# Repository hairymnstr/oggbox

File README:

OggBox
======

Author: nathan@nathandumont.com
License: C code GPL V3, schematics CC-BY-SA 3.0

The OggBox is an open hardware music player.  It supports OggVorbis and WAV files
using a dedicated codec chip from VLSI.  The source code for the main processor
(an ARM Cortex) is written in C and can be found under src/firmware.  You can
compile it with a toolchain built with
https://github.com/esden/summon-arm-toolchain and can be flashed to an STM32 with
the http://code.google.com/p/stm32flash/ executable.  You may need to adjust the
Makefile as the install target uses a specific device on my computer so that it
doesn't try and access any other FTDI devices attached to my PC.

The schematics are in KiCAD format and are under src/sch there's a PDF of the
schematic frozen at the Rev A board production, gerber files for this are in the
src/sch/gerber folder at the moment.  You may need my KiCAD libraries to edit
these files, they're on GitHub too https://github.com/hairymnstr/ndkicadlibrary

Wiki
----

Wiki and blog posts are linked from http://oggbox.nathandumont.com

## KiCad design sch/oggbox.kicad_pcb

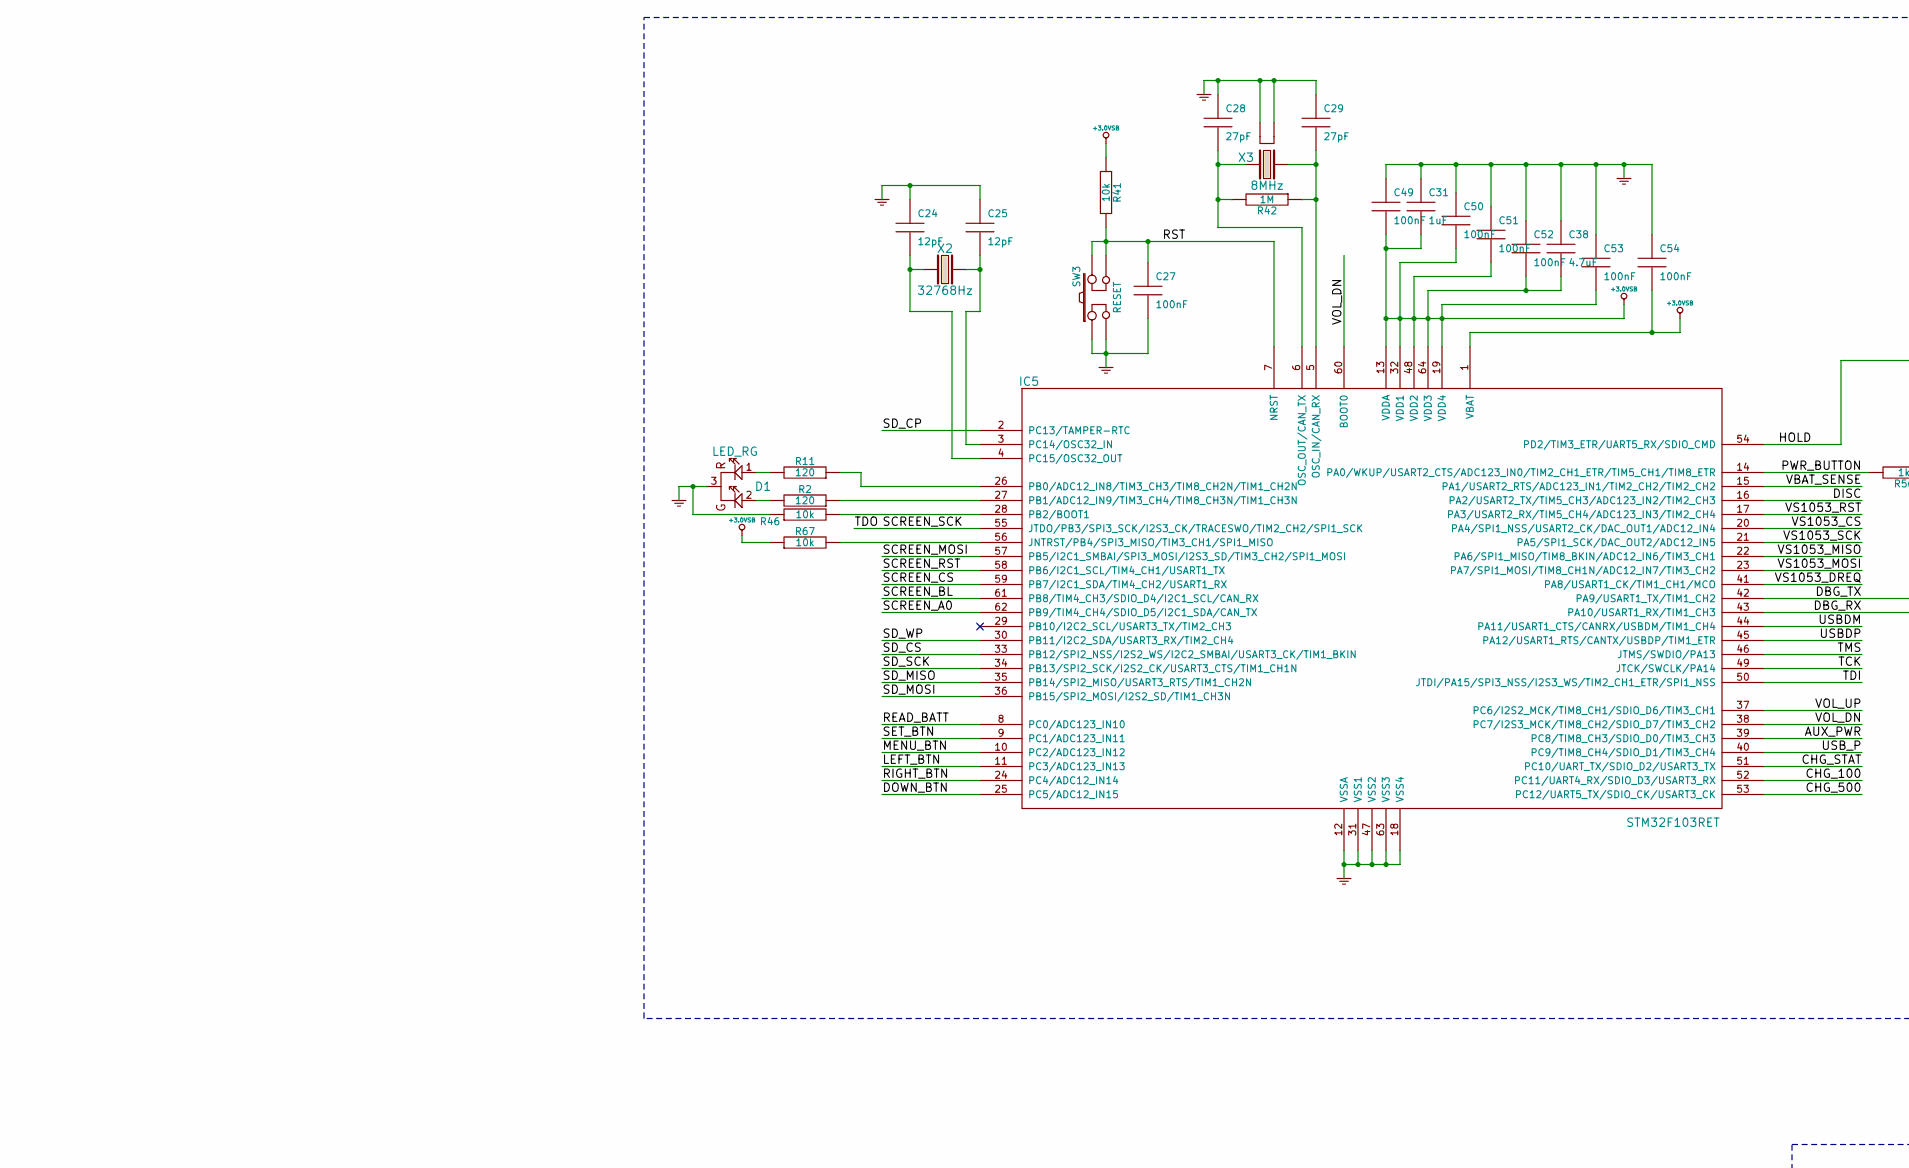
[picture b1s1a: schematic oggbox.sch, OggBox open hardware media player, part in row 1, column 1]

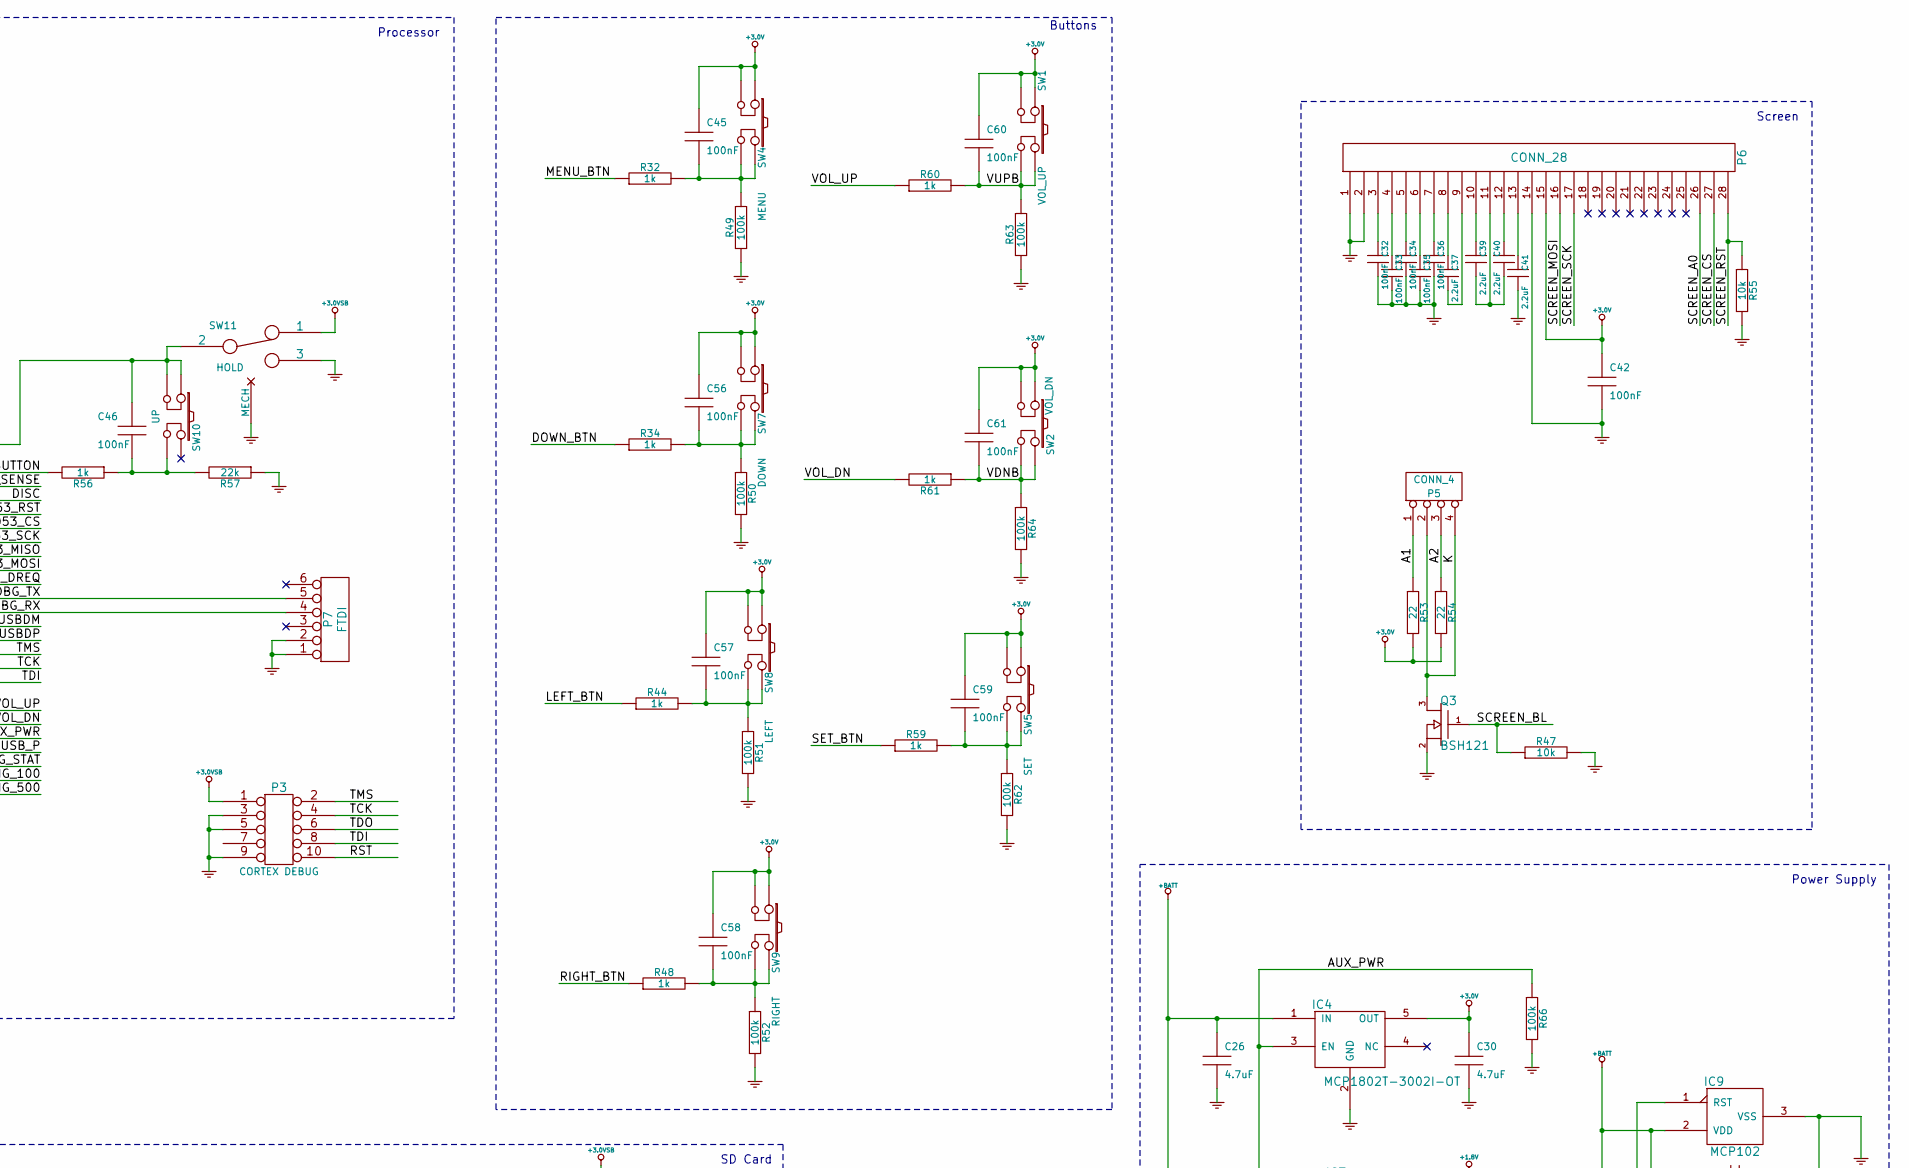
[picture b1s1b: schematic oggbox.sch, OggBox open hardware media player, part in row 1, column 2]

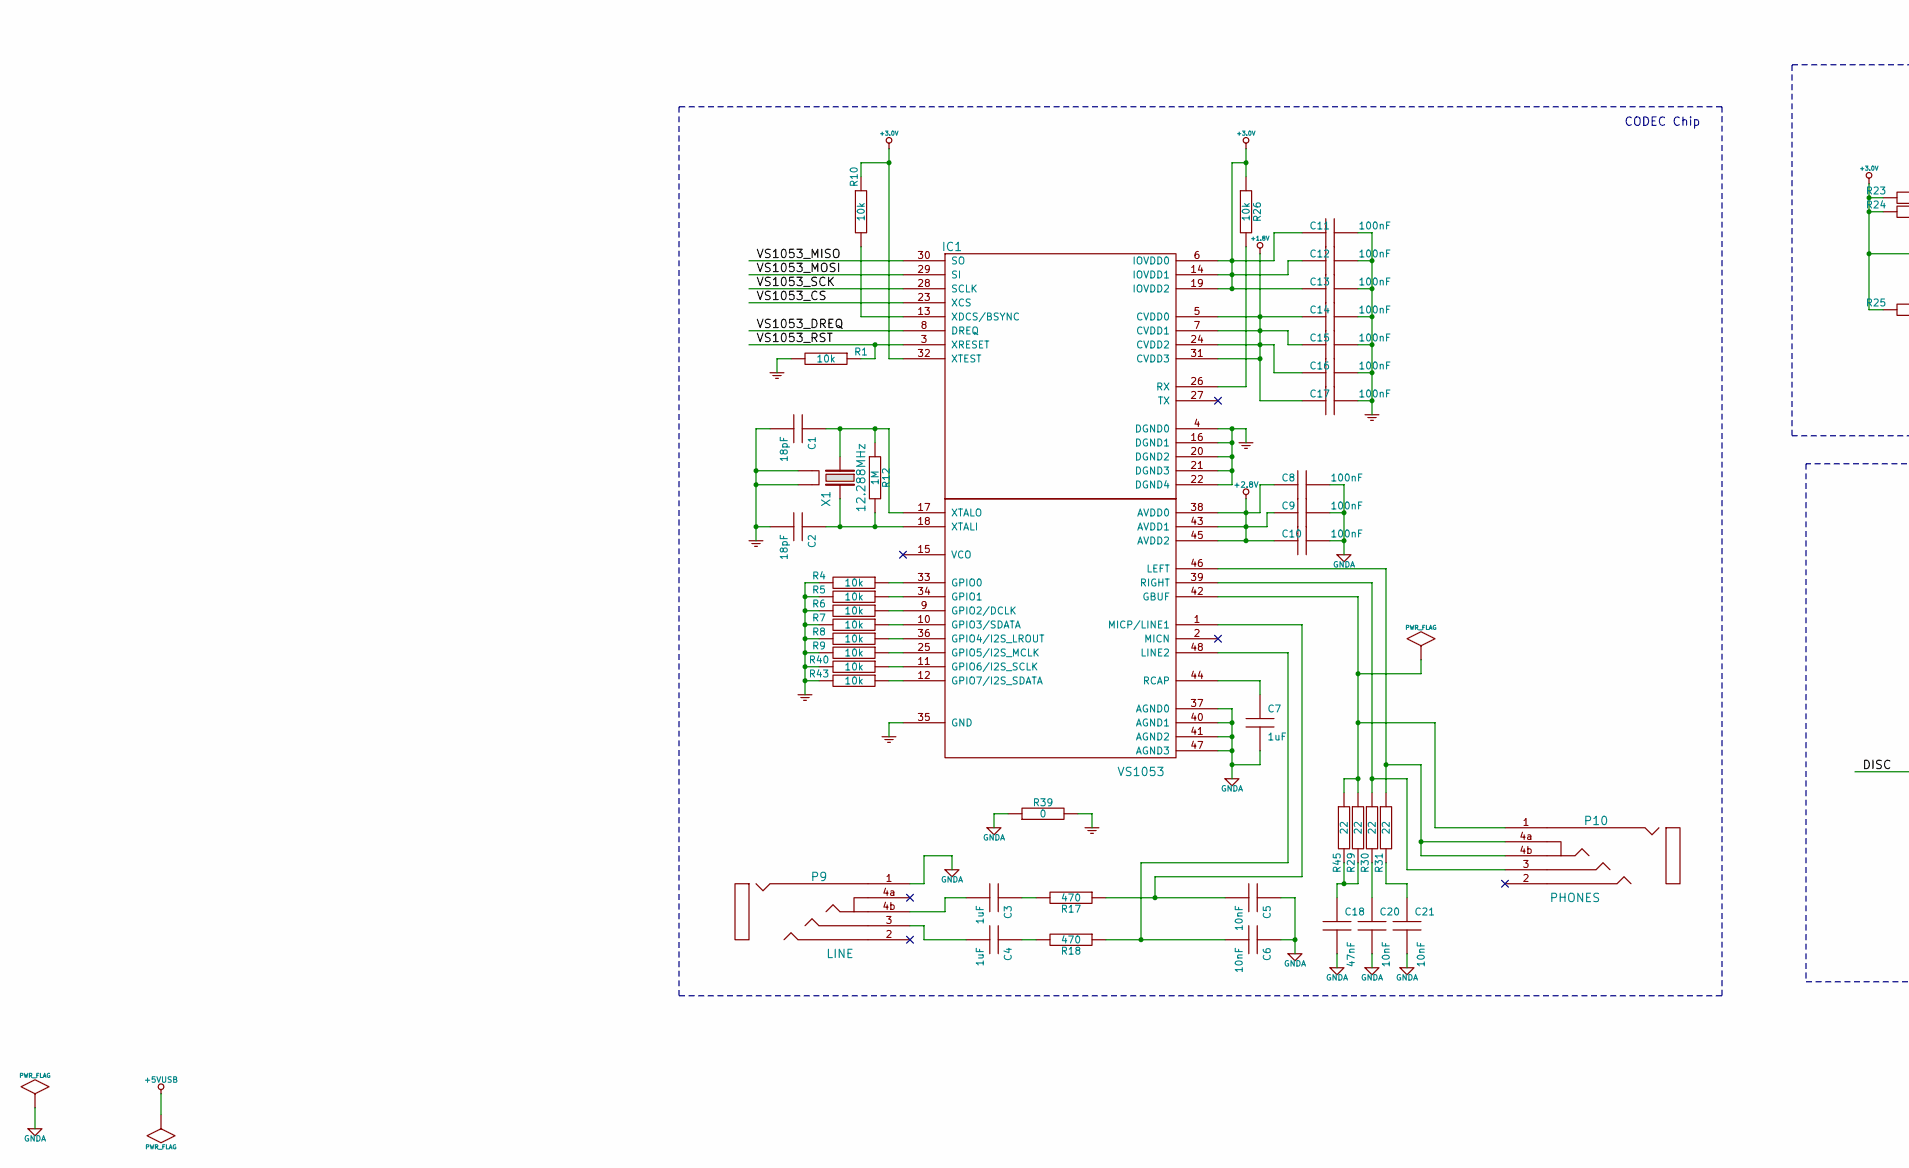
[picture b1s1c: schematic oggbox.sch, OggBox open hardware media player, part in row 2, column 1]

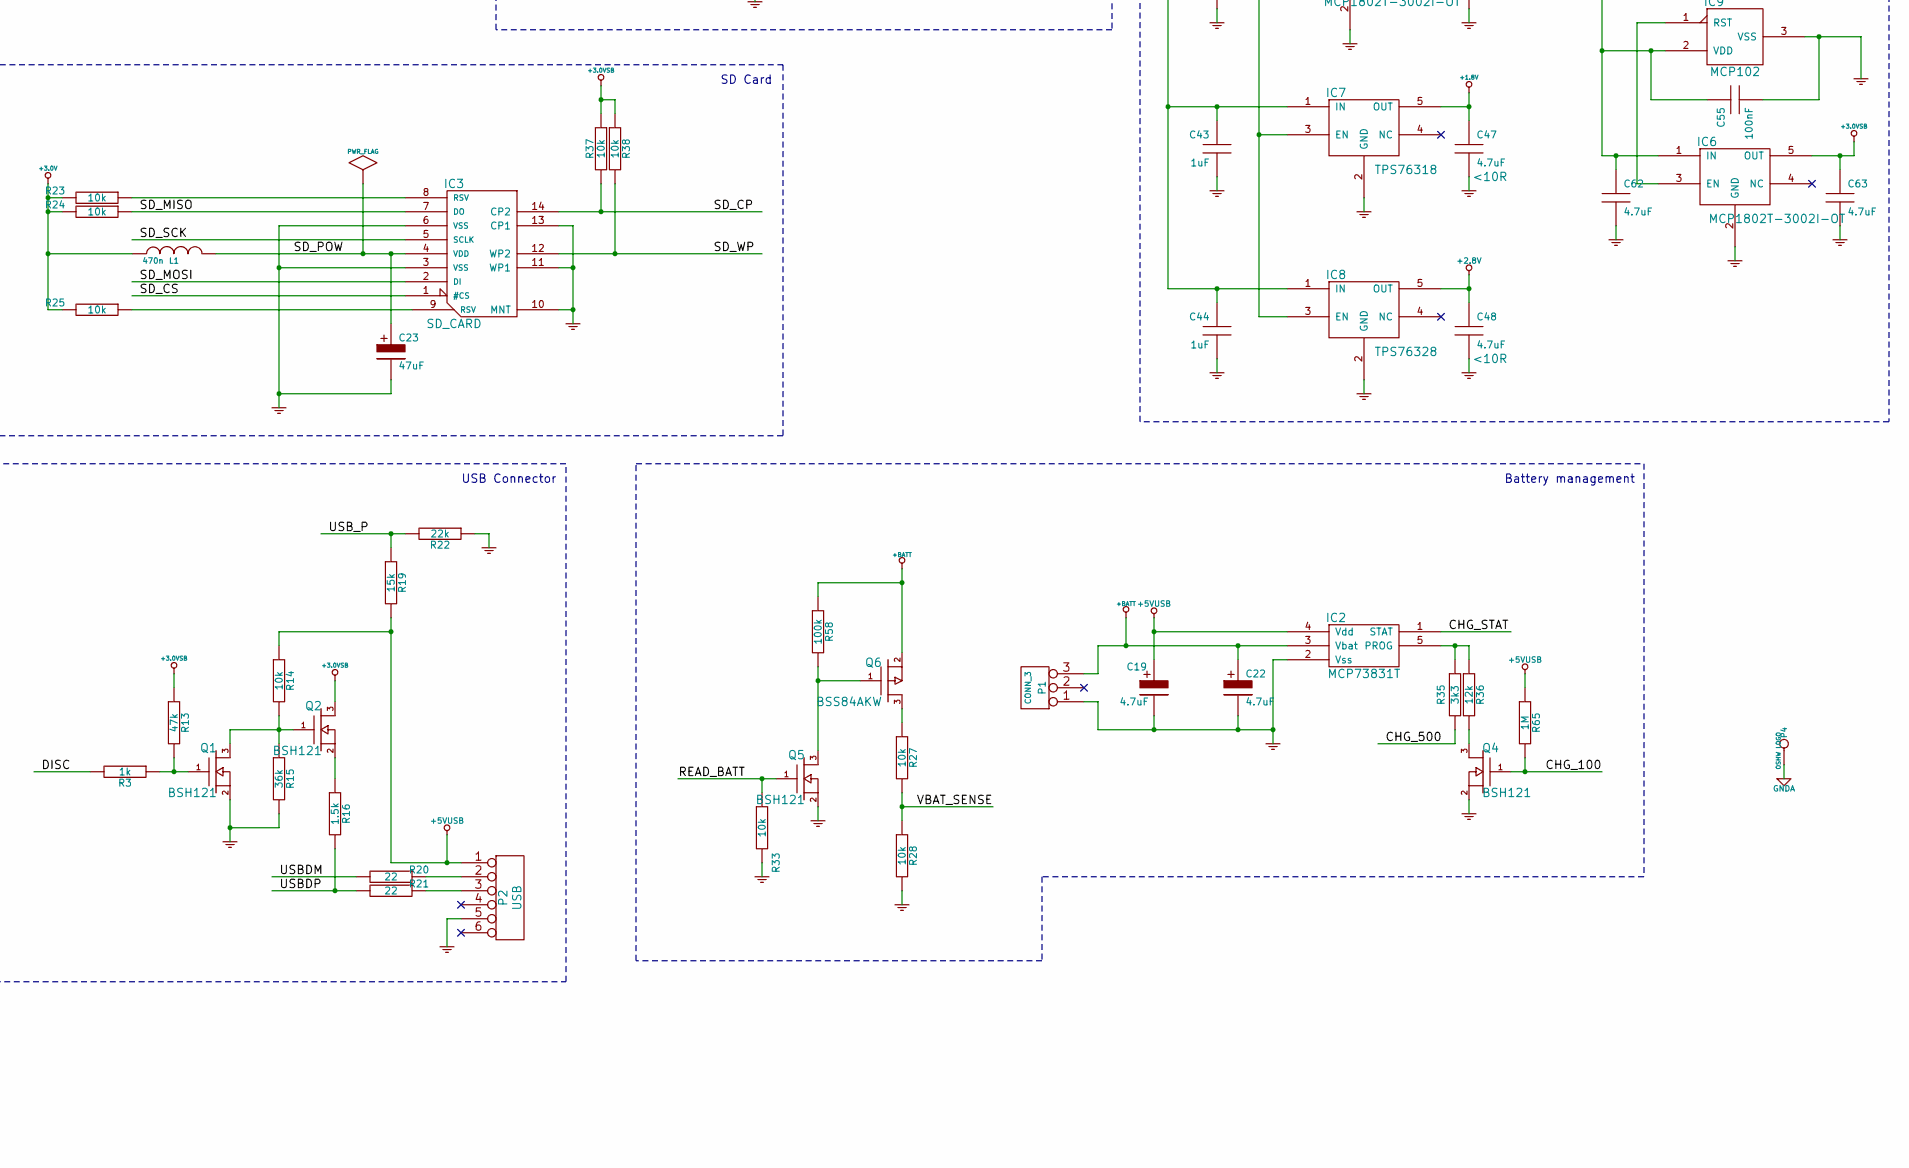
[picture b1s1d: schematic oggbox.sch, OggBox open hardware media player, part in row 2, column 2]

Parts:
C1, C2: 18pF; SM0603
C3, C4, C7, C31, C43, C44: 1uF; SM0603
C5, C6, C20, C21: 10nF; SM0603
C8, C9, C10, C11, C12, C13, C14, C15, C16, C17, C27, C32, C33, C34, C35, C36, C42, C45, C49, C50, C51, C52, C53, C54, C55, C56, C57, C58, C59, C60, C61: 100nF; SM0603
C18: 47nF; SM0603
C19, C22, C26, C30, C38, C47, C48, C62, C63: 4.7uF; SM0805
C23: 47uF; SM1206
C24, C25: 12pF; SM0603; Tolerance 20%; Voltage 50V
C28, C29: 27pF; SM0603
C37, C39, C40, C41: 2.2uF; SM0805
C46: 100nF; SM0603; Tolerance 20%; Voltage 50V
D1: LED_RG; SOT23
IC1: VS1053; LQFP48
IC2: MCP73831T; SOT23-5
IC3: SD_CARD; SD_UNIVERSAL
IC4, IC6: MCP1802T-3002I-OT; SOT23-5
IC5: STM32F103RET; LQFP64
IC7: TPS76318; SOT23-5
IC8: TPS76328; SOT23-5
IC9: MCP102; SOT23
L1: 470n; SM1206
P1: CONN_3; JST_S3B_XHA
P2: USB; MICRO_USB_1568026
P3: CORTEX DEBUG; SAMTEC_SHF-SM_5x2
P4: OSHW LOGO; OSHW_COPPER_10MM
P5: CONN_4; BTHQ128064AVD1
P6: CONN_28; AMP_FPC_28_05MM
P7: FTDI; HEADER_6
P9: LINE; JACK_LUMBERG_1503_13_VP3
P10: PHONES; JACK_LUMBERG_1503_13_VP3
Q1, Q2, Q3, Q4, Q5: BSH121; SOT323
Q6: BSS84AKW; SOT323
R1, R4, R5, R6, R7, R8, R9, R10, R14, R23, R24, R25, R26, R27, R28, R33, R37, R38, R40, R43, R47, R55: 10k; SM0603
R2, R11: 120; SM0603; Tolerance 5%
R3, R32, R34, R44, R48, R59, R60, R61: 1k; SM0603
R12, R42, R65: 1M; SM0603
R13: 47k; SM0603
R15: 36k; SM0603
R16: 1.5k; SM0603
R17, R18: 470; SM0603
R19: 15k; SM0603
R20, R21, R29, R30, R31, R45, R53, R54: 22; SM0603
R22: 22k; SM0603
R35: 3k3; SM0603
R36: 12k; SM0603
R39: 0; SM0603
R41, R46, R67: 10k; SM0603; Tolerance 5%
R49, R50, R51, R52, R58, R62, R63, R64, R66: 100k; SM0603
R56: 1k; SM0603; Tolerance 5%
R57: 22k; SM0603; Tolerance 5%
SW1: VOL_UP; SW_SKQLLCE012
SW2: VOL_DN; SW_SKQLLCE012
SW3: RESET; SW_SKQLLCE012
SW4: MENU; SW_EVQQ2P03W
SW5: SET; SW_EVQQ2P03W
SW7: DOWN; SW_EVQQ2P03W
SW8: LEFT; SW_EVQQ2P03W
SW9: RIGHT; SW_EVQQ2P03W
SW10: UP; SW_EVQQ2P03W
SW11: HOLD; PCM12SMTR
X1: 12.288MHz; CRYSTAL-SMD-5-3_2
X2: 32768Hz; MC306
X3: 8MHz; CRYSTAL-SMD-5-3_2

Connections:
+1.8V: C14.2, C15.2, C16.2, C17.2, C47.1, IC1.5 (CVDD0), IC1.7 (CVDD1), IC1.24 (CVDD2), IC1.31 (CVDD3), IC7.5 (OUT)
+2.8V: C8.2, C9.2, C10.2, C48.1, IC1.38 (AVDD0), IC1.43 (AVDD1), IC1.45 (AVDD2), IC8.5 (OUT)
+3.0V: C11.2, C12.2, C13.2, C30.1, C42.1, C45.1, C56.1, C57.1, C58.1, C59.1, C60.1, C61.1, IC1.6 (IOVDD0), IC1.14 (IOVDD1), IC1.19 (IOVDD2), IC1.32 (XTEST), IC4.5 (OUT), L1.1, P6.15, R10.1, R23.2, R24.2, R25.2, R26.1, R53.2, R54.2, SW1.1, SW1.3, SW2.1, SW2.3, SW4.1, SW4.3, SW5.1, SW5.3, SW7.1, SW7.3, SW8.1, SW8.3, SW9.1, SW9.3
+3.0VSB: C31.2, C38.2, C49.2, C50.2, C51.2, C52.2, C53.2, C54.2, C63.1, IC5.1 (VBAT), IC5.13 (VDDA), IC5.19 (VDD4), IC5.32 (VDD1), IC5.48 (VDD2), IC5.64 (VDD3), IC6.5 (OUT), P3.1, Q2.3 (D), R13.1, R37.1, R38.1, R41.1, R67.1, SW11.1
+5VUSB: C19.1, IC2.4 (Vdd), P2.1, R14.1, R19.2, R65.1
+BATT: C22.1, C26.1, C43.1, C44.1, C55.1, C62.1, IC2.3 (Vbat), IC4.1 (IN), IC6.1 (IN), IC7.1 (IN), IC8.1 (IN), IC9.2 (VDD), P1.3, Q6.2 (S), R58.1
/A1: P5.1, R53.1
/A2: P5.3, R54.1
/AUX_PWR: IC4.3 (EN), IC5.39 (PC8/TIM8_CH3/SDIO_D0/TIM3_CH3), IC7.3 (EN), IC8.3 (EN), R66.1
/CHG_100: IC5.52 (PC11/UART4_RX/SDIO_D3/USART3_RX), Q4.1 (G), R65.2
/CHG_500: IC5.53 (PC12/UART5_TX/SDIO_CK/USART3_CK), R35.2
/CHG_STAT: IC2.1 (STAT), IC5.51 (PC10/UART_TX/SDIO_D2/USART3_TX)
/DBG_RX: IC5.43 (PA10/USART1_RX/TIM1_CH3), P7.4
/DBG_TX: IC5.42 (PA9/USART1_TX/TIM1_CH2), P7.5
/DISC: IC5.16 (PA2/USART2_TX/TIM5_CH3/ADC123_IN2/TIM2_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), R3.2
/DOWN_BTN: IC5.25 (PC5/ADC12_IN15), R34.1
/HOLD: C46.1, IC5.54 (PD2/TIM3_ETR/UART5_RX/SDIO_CMD), SW10.1, SW10.3, SW11.2
/K: P5.2, P5.4, Q3.3 (D)
/LEFT_BTN: IC5.11 (PC3/ADC123_IN13), R44.1
/MENU_BTN: IC5.10 (PC2/ADC123_IN12), R32.1
/PWR_BUTTON: IC5.14 (PA0/WKUP/USART2_CTS/ADC123_IN0/TIM2_CH1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), R56.2
/READ_BATT: IC5.8 (PC0/ADC123_IN10), Q5.1 (G), R33.1
/RIGHT_BTN: IC5.24 (PC4/ADC12_IN14), R48.1
/RST: C27.1, IC5.7 (NRST), P3.10, R41.2, SW3.2, SW3.4
/SCREEN_A0: IC5.62 (PB9/TIM4_CH4/SDIO_D5/I2C1_SDA/CAN_TX), P6.26
/SCREEN_BL: IC5.61 (PB8/TIM4_CH3/SDIO_D4/I2C1_SCL/CAN_RX), Q3.1 (G), R47.1
/SCREEN_CS: IC5.59 (PB7/I2C1_SDA/TIM4_CH2/USART1_RX), P6.27
/SCREEN_MOSI: IC5.57 (PB5/I2C1_SMBAI/SPI3_MOSI/I2S3_SD/TIM3_C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), P6.16
/SCREEN_RST: IC5.58 (PB6/I2C1_SCL/TIM4_CH1/USART1_TX), P6.28, R55.1
/SCREEN_SCK: IC5.55 (JTDO/PB3/SPI3_SCK/I2S3_CK/TRACESWO/TIM2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), P3.6, P6.17
/SD_CP: IC3.14 (CP2), IC5.2 (PC13/TAMPER-RTC), R37.2
/SD_CS: IC3.1 (#CS), IC5.33 (PB12/SPI2_NSS/I2S2_WS/I2C2_SMBAI/USART3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)
/SD_MISO: IC3.7 (DO), IC5.35 (PB14/SPI2_MISO/USART3_RTS/TIM1_CH2N), R24.1
/SD_MOSI: IC3.2 (DI), IC5.36 (PB15/SPI2_MOSI/I2S2_SD/TIM1_CH3N)
/SD_POW: C23.1, IC3.4 (VDD), L1.2
/SD_SCK: IC3.5 (SCLK), IC5.34 (PB13/SPI2_SCK/I2S2_CK/USART3_CTS/TIM1_C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)
/SD_WP: IC3.12 (WP2), IC5.30 (PB11/I2C2_SDA/USART3_RX/TIM2_CH4), R38.2
/SET_BTN: IC5.9 (PC1/ADC123_IN11), R59.1
/TCK: IC5.49 (JTCK/SWCLK/PA14), P3.4
/TDI: IC5.50 (JTDI/PA15/SPI3_NSS/I2S3_WS/TIM2_CH1_ETR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), P3.8
/TMS: IC5.46 (JTMS/SWDIO/PA13), P3.2
/USBDM: IC5.44 (PA11/USART1_CTS/CANRX/USBDM/TIM1_CH4), R20.2
/USBDP: IC5.45 (PA12/USART1_RTS/CANTX/USBDP/TIM1_ETR), R16.2, R21.2
/USB_P: IC5.40 (PC9/TIM8_CH4/SDIO_D1/TIM3_CH4), R19.1, R22.2
/VBAT_SENSE: IC5.15 (PA1/USART2_RTS/ADC123_IN1/TIM2_CH2/TIM2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), R27.2, R28.1
/VDNB: C61.2, R61.1, R64.1, SW2.2, SW2.4
/VOL_DN: IC5.38 (PC7/I2S3_MCK/TIM8_CH2/SDIO_D7/TIM3_CH2), IC5.60 (BOOT0), R61.2
/VOL_UP: IC5.37 (PC6/I2S2_MCK/TIM8_CH1/SDIO_D6/TIM3_CH1), R60.1
/VS1053_CS: IC1.23 (XCS), IC5.20 (PA4/SPI1_NSS/USART2_CK/DAC_OUT1/ADC12_I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)
/VS1053_DREQ: IC1.8 (DREQ), IC5.41 (PA8/USART1_CK/TIM1_CH1/MCO)
/VS1053_MISO: IC1.30 (SO), IC5.22 (PA6/SPI1_MISO/TIM8_BKIN/ADC12_IN6/TIM3_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)
/VS1053_MOSI: IC1.29 (SI), IC5.23 (PA7/SPI1_MOSI/TIM8_CH1N/ADC12_IN7/TIM3_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)
/VS1053_RST: IC1.3 (XRESET), IC5.17 (PA3/USART2_RX/TIM5_CH4/ADC123_IN3/TIM2_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), R1.1
/VS1053_SCK: IC1.28 (SCLK), IC5.21 (PA5/SPI1_SCK/DAC_OUT2/ADC12_IN5)
/VUPB: C60.2, R60.2, R63.2, SW1.2, SW1.4
GND: C1.2, C2.2, C11.1, C12.1, C13.1, C14.1, C15.1, C16.1, C17.1, C19.2, C22.2, C23.2, C24.1, C25.1, C26.2, C27.2, C28.1, C29.1, C30.2, C31.1, C32.2, C33.2, C34.2, C35.2, C36.2, C38.1, C41.2, C42.2, C43.2, C44.2, C47.2, C48.2, C49.1, C50.1, C51.1, C52.1, C53.1, C54.1, C55.2, C62.2, C63.2, D1.3 (GND), IC1.4 (DGND0), IC1.16 (DGND1), IC1.20 (DGND2), IC1.21 (DGND3), IC1.22 (DGND4), IC1.35 (GND), IC2.2 (Vss), IC3.3 (VSS), IC3.6 (VSS), IC3.10 (MNT), IC3.11 (WP1), IC3.13 (CP1), IC4.2 (GND), IC5.12 (VSSA), IC5.18 (VSS4), IC5.31 (VSS1), IC5.47 (VSS2), IC5.63 (VSS3), IC6.2 (GND), IC7.2 (GND), IC8.2 (GND), IC9.3 (VSS), P1.1, P2.5, P3.3, P3.5, P3.9, P6.1, P6.2, P6.14, P7.1, P7.2, Q1.2 (S), Q3.2 (S), Q4.2 (S), Q5.2 (S), R1.2, R4.2, R5.2, R6.2, R7.2, R8.2, R9.2, R15.2, R22.1, R28.2, R33.2, R39.2, R40.2, R43.2, R46.1, R47.2, R49.1, R50.2, R51.2, R52.2, R55.2, R57.1, R62.2, R63.1, R64.2, R66.2, SW3.1, SW3.3, SW11.3, SW11.4 (MECH), X1.2 (GND), X1.4 (GND), X3.2 (GND), X3.4 (GND)
GNDA: C5.1, C6.1, C7.2, C8.1, C9.1, C10.1, C18.2, C20.2, C21.2, IC1.37 (AGND0), IC1.40 (AGND1), IC1.41 (AGND2), IC1.47 (AGND3), P4.1, P9.1, R39.1
unnamed: IC3.9 (RSV), R25.1
unnamed: IC3.8 (RSV), R23.1
unnamed: C25.2, IC5.3 (PC14/OSC32_IN), X2.1
unnamed: C24.2, IC5.4 (PC15/OSC32_OUT), X2.2
unnamed: IC5.27 (PB1/ADC12_IN9/TIM3_CH4/TIM8_CH3N/TIM1_C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), R2.1
unnamed: IC5.28 (PB2/BOOT1), R46.2
unnamed: Q1.1 (G), R3.1, R13.2
unnamed: C46.2, R56.1, R57.2, SW10.4
unnamed: IC1.11 (GPIO6/I2S_SCLK), R40.1
unnamed: IC1.10 (GPIO3/SDATA), R7.1
unnamed: IC1.9 (GPIO2/DCLK), R6.1
unnamed: C5.2, IC1.1 (MICP/LINE1), R17.1
unnamed: C1.1, IC1.17 (XTALO), R12.1, X1.1
unnamed: IC1.34 (GPIO1), R5.1
unnamed: IC1.36 (GPIO4/I2S_LROUT), R8.1
unnamed: IC1.26 (RX), R26.2
unnamed: IC1.25 (GPIO5/I2S_MCLK), R9.1
unnamed: C7.1, IC1.44 (RCAP)
unnamed: IC1.33 (GPIO0), R4.1
unnamed: IC1.12 (GPIO7/I2S_SDATA), R43.1
unnamed: Q6.3 (D), R27.1
unnamed: Q5.3 (D), Q6.1 (G), R58.2
unnamed: Q4.3 (D), R36.2
unnamed: P2.3, R21.1
unnamed: P2.2, R20.1
unnamed: C28.2, IC5.6 (OSC_OUT/CAN_TX), R42.2, X3.3
unnamed: IC6.3 (EN), IC9.1 (RST)
unnamed: Q1.3 (D), Q2.1 (G), R14.2, R15.1
unnamed: Q2.2 (S), R16.1
unnamed: IC5.56 (JNTRST/PB4/SPI3_MISO/TIM3_CH1/SPI1_MISO), R67.2
unnamed: C2.1, IC1.18 (XTALI), R12.2, X1.3
unnamed: C29.2, IC5.5 (OSC_IN/CAN_RX), R42.1, X3.1
unnamed: C45.2, R32.2, R49.2, SW4.2, SW4.4
unnamed: C59.2, R59.2, R62.1, SW5.2, SW5.4
unnamed: C58.2, R48.2, R52.1, SW9.2, SW9.4
unnamed: C56.2, R34.2, R50.1, SW7.2, SW7.4
unnamed: C57.2, R44.2, R51.1, SW8.2, SW8.4
unnamed: IC2.5 (PROG), R35.1, R36.1
unnamed: D1.2 (GRN), R2.2
unnamed: C4.1, R18.2
unnamed: C36.1, P6.7
unnamed: C21.1, R31.2
unnamed: C6.2, IC1.48 (LINE2), R18.1
unnamed: IC1.46 (LEFT), P10.4a, P10.4b, R31.1
unnamed: C40.1, P6.12
unnamed: C39.1, P6.10
unnamed: C37.2, P6.9
unnamed: C32.1, P6.3
unnamed: C34.1, P6.5
unnamed: C39.2, C40.2, P6.11
unnamed: C41.1, P6.13
unnamed: C4.2, P9.3
unnamed: C20.1, R30.2
unnamed: C3.1, R17.2
unnamed: D1.1 (RED), R11.2
unnamed: C35.1, P6.6
unnamed: C33.1, P6.4
unnamed: C37.1, P6.8
unnamed: C3.2, P9.4b
unnamed: IC1.42 (GBUF), P10.1, R29.1, R45.1
unnamed: IC1.39 (RIGHT), P10.3, R30.1
unnamed: IC1.13 (XDCS/BSYNC), R10.2
unnamed: IC5.26 (PB0/ADC12_IN8/TIM3_CH3/TIM8_CH2N/TIM1_C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), R11.1
unnamed: C18.1, R29.2, R45.2

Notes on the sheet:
CODEC Chip
SD Card
USB Connector
Battery management
Power Supply
Screen
Buttons
Processor

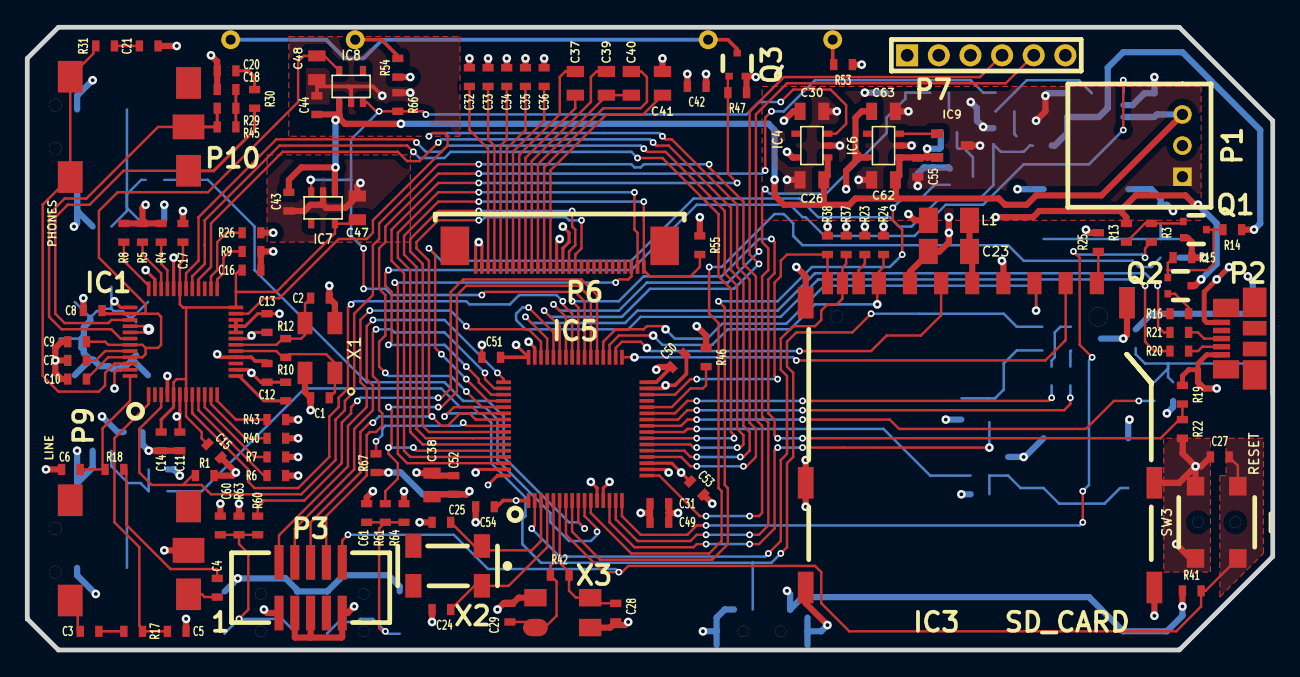
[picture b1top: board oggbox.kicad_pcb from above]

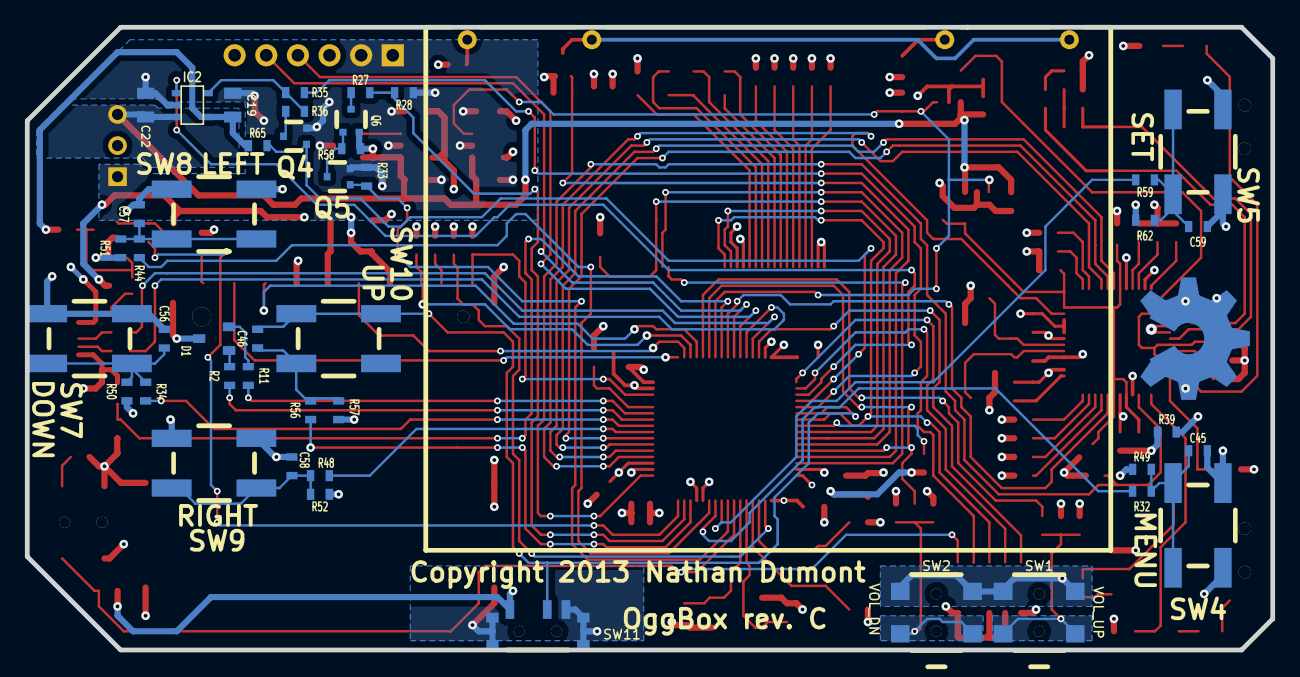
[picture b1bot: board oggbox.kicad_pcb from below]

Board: 4 copper layers, 100.0 x 50.0 mm, 169 parts (46 on the bottom side), 121 nets.

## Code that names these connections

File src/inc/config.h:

/*
 * config.h
 *
 * Contains all the hardware specific configuration and pin definitions
 */
#ifndef OGGBOX_H
#define OGGBOX_H 1

// SD card interface
#define SD_SPI        SPI2
#define SD_PORT       GPIOB
#define SD_CS_PIN     GPIO12
#define SD_MOSI_PIN   GPIO15
#define SD_MISO_PIN   GPIO14
#define SD_SCK_PIN    GPIO13
#define SD_WP_PIN     GPIO11
#define SD_WP_PORT    GPIOB
#define SD_CP_PIN     GPIO13
#define SD_CP_PORT    GPIOC

#define SD_SPI_APB    RCC_APB1ENR
#define SD_RCC_SPI    RCC_APB1ENR_SPI2EN
#define SD_IO_APB     RCC_APB2ENR
#define SD_RCC_IO     RCC_APB2ENR_IOPBEN

// LED indicator
#define GREEN_LED_PORT GPIOB
#define GREEN_LED_PIN GPIO1
#define RED_LED_PORT GPIOB
#define RED_LED_PIN GPIO0

// LCD pins
#define LCD_CS_PORT   GPIOB
#define LCD_CS_PIN    GPIO7
#define LCD_RST_PORT  GPIOB
#define LCD_RST_PIN   GPIO6
#define LCD_BL_PORT   GPIOB
#define LCD_BL_PIN    GPIO8
#define LCD_DC_PORT   GPIOB
#define LCD_DC_PIN    GPIO9
#define LCD_MOSI_PORT GPIOB
#define LCD_MOSI_PIN  GPIO5
#define LCD_SCK_PORT  GPIOB
#define LCD_SCK_PIN   GPIO3

#define LCD_SPI       SPI3

// codec hardware
#define CODEC_PORT      GPIOA
#define CODEC_CS        GPIO4
#define CODEC_SCK       GPIO5
#define CODEC_MISO      GPIO6
#define CODEC_MOSI      GPIO7

#define CODEC_DREQ_PORT GPIOA
#define CODEC_DREQ      GPIO8
#define CODEC_RST_PORT  GPIOA
#define CODEC_RST       GPIO3
#define CODEC_PWR_PORT  GPIOB
#define CODEC_PWR       GPIO5

#define CODEC_IOS_APB   RCC_APB2ENR
#define CODEC_RCC_IOS   RCC_APB2ENR_IOPAEN

#define CODEC_PWR_APB   RCC_APB2ENR
#define CODEC_RCC_PWR   RCC_APB2ENR_IOPBEN

#define CODEC_IOI_APB   RCC_APB2ENR
#define CODEC_RCC_IOI   RCC_APB2ENR_IOPCEN

#define CODEC_SPI       SPI1
#define CODEC_SPI_APB   RCC_APB2ENR
#define CODEC_RCC_SPI   RCC_APB2ENR_SPI1EN

// Power management
#define AUX_POWER_PORT GPIOC
#define AUX_POWER_PIN GPIO8

#define BAT_CHK_PORT  GPIOC
#define BAT_CHK_PIN   GPIO0

#define BAT_VAL_PORT  GPIOA
#define BAT_VAL_PIN   GPIO1

#define USB_P_PORT    GPIOC
#define USB_P_PIN     GPIO9

#define CHG_STAT_PORT GPIOC
#define CHG_STAT_PIN  GPIO10

#define CHG_100_PORT  GPIOC
#define CHG_100_PIN   GPIO11

#define CHG_500_PORT  GPIOC
#define CHG_500_PIN   GPIO12

// Button definitions
#define VOL_UP_PORT     GPIOC
#define VOL_UP_PIN      GPIO6

#define VOL_DOWN_PORT   GPIOC
#define VOL_DOWN_PIN    GPIO7

#define MENU_BTN_PORT   GPIOC
#define MENU_BTN_PIN    GPIO2

#define SET_BTN_PORT    GPIOC
#define SET_BTN_PIN     GPIO1

#define UP_BTN_PORT     GPIOA
#define UP_BTN_PIN      GPIO0

#define LEFT_BTN_PORT   GPIOC
#define LEFT_BTN_PIN    GPIO3

#define RIGHT_BTN_PORT  GPIOC
#define RIGHT_BTN_PIN   GPIO4

#define DOWN_BTN_PORT   GPIOC
#define DOWN_BTN_PIN    GPIO5

// USB stuff
#define USB_DISC_PORT   GPIOA
#define USB_DISC_PIN    GPIO2

// stdio definitions
#define STD_OUT_UART  USART1
#define STD_ERR_UART  USART1
#define STD_IN_UART   USART1

#endif /* ifndef OGGBOX_H */

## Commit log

2010-11-28 Initial commit, working "hello_world" over uart for oggbox
2010-12-07 Screen brightness control working in demo loop.
2010-12-08 Fixed a bug in itoa and started screen printing, doesn't work though.
2010-12-14 Screen works, hardware bug with contrast now. itoa bugs fixed again
2011-01-12 Added high level set/get for row/col/inv and print functions to screen.
2011-01-15 Created a font based on IBM code page 437. Print to screen now works.
2012-02-19 Added schematic to git, about to annotate and start PCB
2012-05-17 Forgot to keep git up to date, loads of updates.
2012-05-17 More PCB routing, removed some unneccessary stuff and tidied up the charger circuit. Bi colour LED now on the STM32 not VS1053
2012-05-17 Corrected a USB pinout bug in schematic and netlist. Re-arranging power/USB wiring.
2012-05-17 More routing on the PCB. Making some progress slowly.
2012-05-17 More routing.
2012-05-21 More routing. Some schematic fixes, now 3.0V not 3.3V
2012-05-22 100% routed!
2012-05-22 Clean up tracks/vias
2012-05-22 More fiddling with tracks
2012-05-23 Added some silk screen stuff
2012-05-23 Tidied up all the silk screen should be ready for manufacture.
2012-05-23 Fixed volume button labels.
2012-05-23 Changed the drill hole to PTH on side switches
2012-05-23 Version that was sent to iTead for manufacture.
2012-06-02 Back annotated footprints for faster BOM generation
2012-06-09 Sorting out code directory ready for Rev A firmware
2012-06-09 Makefile setup for building the blink example code here
2012-06-10 Started the pin naming header and added install target
2012-06-10 Working basic LCD library based on the ChipKIT code.
2012-06-16 More screen work, now prints "OggBox RevA" on screen.
2012-06-18 Got the hold switch attached and connected to the red LED.
2012-06-27 Trying to get the stdio stuff working. Failing so far.
2012-07-04 Still failing to get the stdio stuff working.
2012-07-07 Working syscalls, it was a toolchain problem.
2012-07-08 Added the codec control library, testing now
2012-07-08 Trying to get MP3 working, very quiet and distorted still though
2012-07-10 Working on some sort of power problem
2012-07-10 Added some testing code for the meta data library
2012-07-11 Working on the database code more
2012-07-11 Got it working, hardware mistake. Still high current problems
2012-07-12 Python model of BTree database working, trying an in-memory C implementation before moving to SD card
2012-07-13 C implementation of primitive database working in memory
2012-07-13 Committed RevA to PDF and started moding schematic for RevB
2012-07-13 Making an attempt at handling actual tag data in the database now.
2012-07-19 Implemented a simple Galois LFSR pseudo-random number source for shuffled playlists
2012-07-26 Working on RevB schematic a bit more. PSU redesign.
2012-07-27 Added the starts of a simple job scheduler
2012-07-27 More work on the job scheduler
2012-08-01 Working on making the player run asynchronously
2012-08-02 More work on the asynchronous media player.
2012-08-03 Asynchronous player now working correctly.
2012-08-03 Little addition to calculate ogg track lengths in milliseconds
2012-08-09 Added progress meter (untested) plus some tidying up
2012-08-09 Working on UI found that seek isn't implemented and started implementing.
2012-08-14 Added a README for GitHub
2012-08-14 Re-fromatted the README a bit
2012-08-16 Working on the seek call
2012-08-16 Sorted seek I think, needs to go much faster
2012-08-17 Working on improving speed of ogg_id function, now all un-buffered. Lseek implementation in sdfat has been optimised for same sector and same-cluster seeks.
2012-08-17 Working for OggCamp, can't play less than 192kbps because of blocking interrupts not reading disk sectors
2012-09-05 Working on the SD card blocking problem, doesn't work at the moment.
2012-09-11 Still working on SD card blocking problems
2012-09-11 Now working. codec IRQ needs priority 16+ to avoid interrupting SD DMA
2012-09-11 Sorting through all the compile warnings
2012-09-11 More tidying the source. Still works
2012-09-11 Adding a more portable structure to SD card DMA
2012-09-13 Rolled back sd.c to try blocking version again now IRQ priorities should be sorted
2012-09-13 Now compiling again. reverted to a blocking SD access model
2012-09-13 Moved an extra call to multiblock
2012-09-20 Preparing to lay out Rev B board
2012-09-22 Re-routed the power supply control for RevB
2012-09-22 Placed new resistors for RevB
2012-09-23 Changed the side switches to new footprint, not routed.
2012-09-23 Routed the new volume switches
2012-09-23 Changed the footprint of the RTC crystal to an SMD part
2012-09-23 Re-routed all the power supply around the newly placed serial header
2012-09-24 Moving stuff around to try and shift the SD socket
2012-09-24 Re-routed all the power to fit new reset switch, SD socket still needs moving
2012-09-24 Moved the SD card socket back 3mm
2012-09-24 Moved another 0.5mm to make sure the LED is clear of the mounting holes on the SD socket
2012-09-24 Added option to use goodluckbuy SD sockets
2012-09-24 Added extra decoupling and updated silkscreen
2012-09-25 Tidied up the silkscreen layout for manufacture
2012-09-25 Tinkering with ground plane and 3D models
2012-09-26 Final tweaks ready to make gerbers and order a RevB board
2012-09-26 Moved rev A gerbers to a separate file, might be handy to keep them in trunk
2012-09-26 Final edits of Rev B, now submitted for manufacture
2012-12-12 Started re-licensing as LGPLv3 to allow re-use of parts in closed products
2012-12-12 Updated license in README file
2012-12-13 Working on abstracting block layer functions for filesystem access
2012-12-13 Preparing to test the new block based mount
2012-12-17 Lots more unit tests on filesystem stuff, and plenty of bug fixing
2012-12-18 Added an md5 hash function to help with unit tests on filesystem stuff
2012-12-18 Started work on writeable filesystem, cleaned up files in memory
2012-12-18 First pass at writing a fat_write function, untested
2012-12-18 Tidying up definitions of read and write
2012-12-18 Started putting proper error handling into read and write
2012-12-18 close is now posix compliant with errors etc.
2012-12-18 Added handling to find and allocate new clusters
2012-12-18 Sorting out the file read/write flags
2012-12-20 Added some device read only permissions handling
2012-12-20 A bit of tidying up.
2012-12-20 Added part of the code to create new files
2012-12-20 First implementation of freeing cluster chain
2012-12-20 Replacing non file access using file buffers with one global sysbuf
2012-12-20 Found a bug in mount, sectors_per_fat was not properly initialised.
2012-12-20 Now writes a readable file to the root directory. Needs testing.
2012-12-21 Fixed 2 bugs with closing/error exits on fat_open()
2012-12-21 Removed all handling of folder readonly status, ignored by Windows apparently
2012-12-21 Removed final SD specific naming
2012-12-21 Fixed some more bugs, the PNG file copy experiment produces a valid file but it isn't readable
2012-12-26 Fixed an extra cluster seek when writing new files.
2013-01-03 Started writing the block driver for the ARM platform
2013-02-22 Started the Rev C schematic, just changed the battery voltage check switch to a P type MOSFET
2013-02-25 Started laying out the Rev C board
2013-02-26 Made some more schematic revisions for the Rev C
2013-07-24 Oggbox Rev C almost ready to order!
2013-08-03 Ready to order the Rev C PCBs.
2013-08-05 Final changes for the Rev C board order.
2013-08-17 Started working on the firmware for Rev C. Introducing the new FAT routines with abstracted block layer. Rewritten the linker script for the STM32F103RET6
2013-08-27 Moving source tree around about to start working on RTOS stuff. Currently does play a file
2013-08-27 Added the FreeRTOS source code I think I need
2013-08-28 Blinking the green LED in a thread in FreeRTOS
2013-08-28 Minimal setup working to play a demo file under FreeRTOS, a bit of a mess at the moment, but it works.
2013-08-29 Started the power management task, checks battery voltage currently
2013-08-30 Added volume control with a message queue.
2013-08-31 Added the basic screen driver and got USB charging working with basic USB serial emulation
2013-09-01 Lots of work on screen driver and UI, displays artist, track and album and scrolls if they don't fit on screen. Ogg meta information imported from the old source.
2013-09-03 Got a rudimentary playlist working so it plays all files on the card.
2013-09-04 Started the main menu and some new line drawing fucntions to help with menu drawing.
2013-09-05 Finished off the box drawing routines.
2013-09-07 More menu stuff.
2013-09-09 Sorted out a proper 8x6 font. Might tweak a little more but much better than it was.
2013-09-12 Fixed a couple of edge case for FAT16 handling in the FAT library
2013-09-13 Started work on a case design, so far just roughing-out the PCBA as a 3D model
2013-09-19 More cad stuff and a functional UTF-8 to Ascii converter for removing accents from meta tags.
2013-10-05 Massive heap of new code to do with database creation
2013-10-06 Now shuts down to ~600uA standby mode if you hold up button, then wakes up if you press up again
2013-10-10 Now indexes artists, tracks and albums using btree
2013-11-20 Just switched over to a markdown file for the readme
2014-07-28 Removed the now obsolete freertos version of libopencm3 and linking against an unmodified version of libopencm3. The necessary changes are made in my FreeRTOS port.c file now.
2014-07-30 Now actually works with standard checkout of modern libopencm3
2014-07-30 Out of tree build now working.
2016-03-18 Rearranging the source tree again
2016-03-18 Renamed src to firmware to clear things up a bit and started adding dependencies under the new lib folder
2016-03-18 Added the libopencm3 library to the new lib folder
2016-03-19 Added freertos submodule
2016-03-19 moved the gristle submodule to the right place
2016-03-19 Removing rongly placed gristle sumodule
2016-03-22 Added the gristle submodule in the correct place.
2017-02-25 Another big re-arranging of the source tree. Migrated to the proper release of FreeRTOS 9 and got the libopencm3 <-> FreeRTOS interaction working without editting the source of either.
2019-10-03 Migrated the oggbox to KiCad 5.x with all local libraries
2019-10-03 Updated license to BSD and CC0 to simplify reuse for embedded (statically linked) projects. Updated readme info.
2019-10-11 Updated the OggBox project to work with KiCad v5, made it a demo for automated manufacturing outputs
2019-10-11 Updating the library to a consistent state.

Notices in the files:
sch/oggbox.kicad_pcb:
Copyright 2013 Nathan Dumont
